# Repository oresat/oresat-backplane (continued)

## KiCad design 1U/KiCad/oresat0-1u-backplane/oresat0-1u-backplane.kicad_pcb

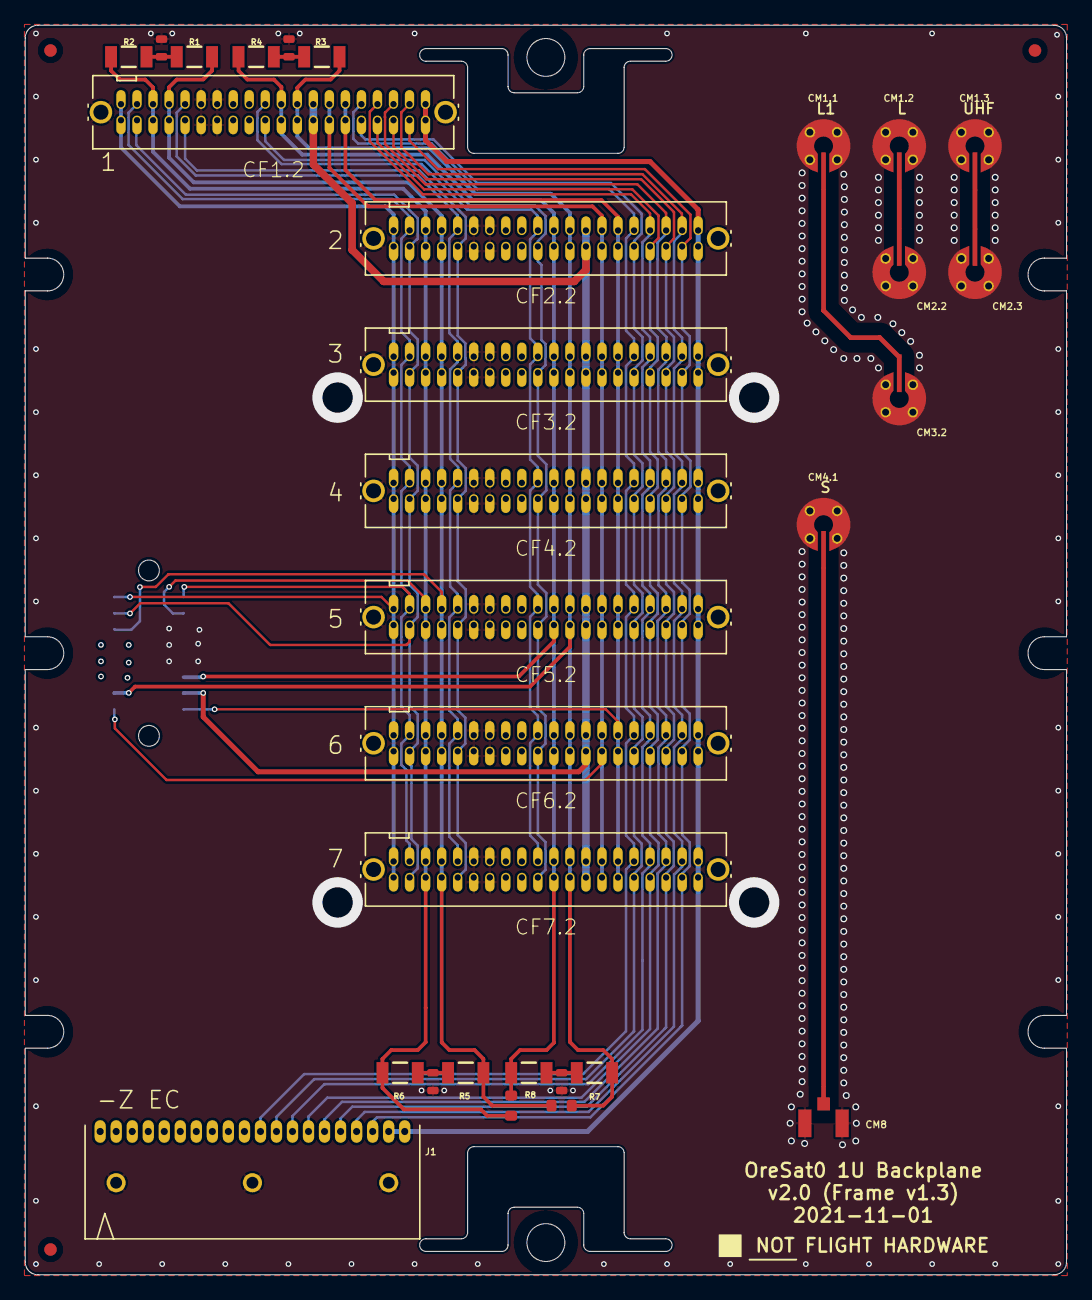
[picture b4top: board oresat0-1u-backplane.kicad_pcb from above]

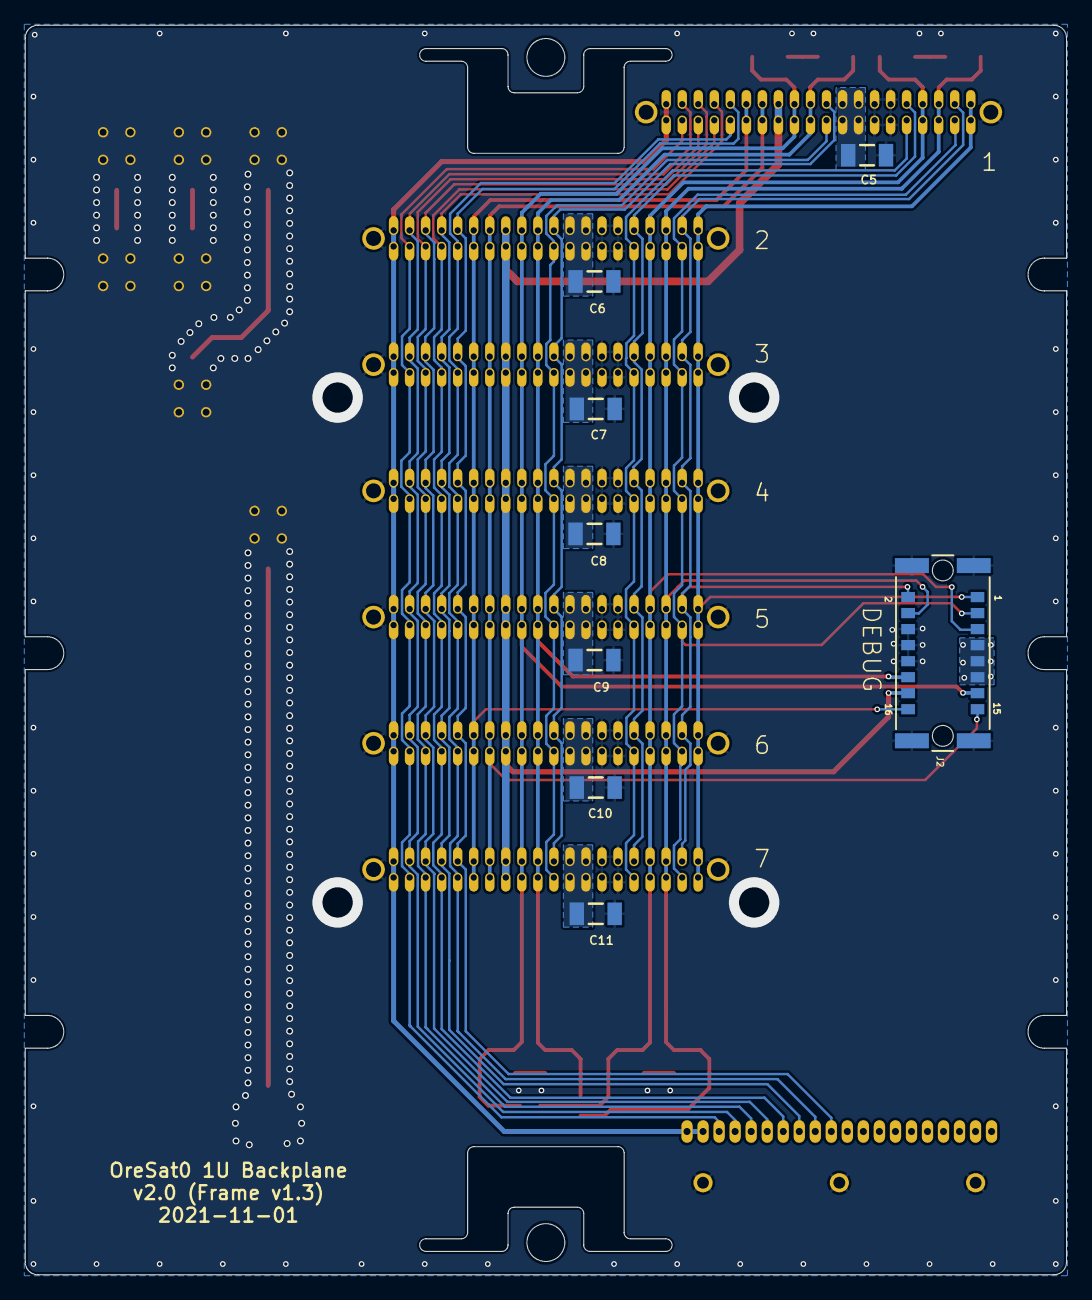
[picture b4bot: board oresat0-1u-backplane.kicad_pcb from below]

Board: 4 copper layers, 82.5 x 99.0 mm, 44 parts (8 on the bottom side), 33 nets.

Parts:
@HOLE0, @HOLE1: (no value)
C1, C2, C3, C4: 1n; .0603-C-NOSILK
C5, C6, C7, C8, C9, C10, C11: 10u 25V; 1206-B
CF1.2, CF2.2, CF3.2, CF4.2, CF5.2, CF6.2, CF7.2: SFM-120-X1-XXX-D
CM1.1, CM1.2, CM1.3, CM2.2, CM2.3, CM3.2, CM4.1: J-MOLEX-SMPM-73300-0111X; J-MOLEX-SMPM-73300-0111X-long
CM8: U.FL-R-SMA; U.FL-R-SMT
FIDUCIAL1, FIDUCIAL2, FIDUCIAL3: FIDUCIAL-1.0X2.0
J1: 5-104196-5
J2: M55-6001642R; CONN_M55-6001642R_HRW
R1, R2, R3, R4: 60.4; 1206-C
R5, R6, R7, R8: NP/60.4; 1206-C
R9, R10: 0; .0603-B-NOSILK
U$1: FLIGHMARKERNEW; FLIGHTMARKER_NEW_BOARDS

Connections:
C3-UART-RX: CF1.2.38, CF2.2.38, CF3.2.38, CF4.2.38, CF5.2.38, CF6.2.38, CF7.2.38, J2.2
C3-UART-TX: CF1.2.37, CF2.2.37, CF3.2.37, CF4.2.37, CF5.2.37, CF6.2.37, CF7.2.37, J2.3
CAN1_H: CF1.2.33, CF1.2.34, CF2.2.33, CF2.2.34, CF3.2.33, CF3.2.34, CF4.2.33, CF4.2.34, CF5.2.33, CF5.2.34, CF6.2.33, CF6.2.34, CF7.2.33, CF7.2.34, J2.5, R1.1, R5.1, R10.1
CAN1_L: CF1.2.35, CF1.2.36, CF2.2.35, CF2.2.36, CF3.2.35, CF3.2.36, CF4.2.35, CF4.2.36, CF5.2.35, CF5.2.36, CF6.2.35, CF6.2.36, CF7.2.35, CF7.2.36, J2.4, R2.1, R6.1, R9.1
CAN2_H: CF1.2.17, CF1.2.18, CF2.2.17, CF2.2.18, CF3.2.17, CF3.2.18, CF4.2.17, CF4.2.18, CF5.2.17, CF5.2.18, CF6.2.17, CF6.2.18, CF7.2.17, CF7.2.18, J2.13, R3.1, R7.1, R10.2
CAN2_L: CF1.2.19, CF1.2.20, CF2.2.19, CF2.2.20, CF3.2.19, CF3.2.20, CF4.2.19, CF4.2.20, CF5.2.19, CF5.2.20, CF6.2.19, CF6.2.20, CF7.2.19, CF7.2.20, J2.12, R4.1, R8.1, R9.2
GND: C1.2, C2.2, C3.2, C4.2, C5.2, C6.2, C7.2, C8.2, C9.2, C10.2, C11.2, CF1.2.27, CF1.2.28, CF1.2.29, CF1.2.30, CF1.2.LC1, CF1.2.LC2, CF2.2.27, CF2.2.28, CF2.2.29, CF2.2.30, CF2.2.LC1, CF2.2.LC2, CF3.2.27, CF3.2.28, CF3.2.29, CF3.2.30, CF3.2.LC1, CF3.2.LC2, CF4.2.27, CF4.2.28, CF4.2.29, CF4.2.30, CF4.2.LC1, CF4.2.LC2, CF5.2.27, CF5.2.28, CF5.2.29, CF5.2.30, CF5.2.LC1, CF5.2.LC2, CF6.2.27, CF6.2.28, CF6.2.29, CF6.2.30, CF6.2.LC1, CF6.2.LC2, CF7.2.27, CF7.2.28, CF7.2.29, CF7.2.30, CF7.2.LC1, CF7.2.LC2, CM1.1.GND (SHIELD1), CM1.2.GND (SHIELD1), CM1.3.GND (SHIELD1), CM2.2.GND (SHIELD1), CM2.3.GND (SHIELD1), CM3.2.GND (SHIELD1), CM4.1.GND (SHIELD1), CM8.2, CM8.3, J1.HD1 (HD), J1.HD2 (HD), J1.HD3 (HD), J2.6, J2.8, J2.10, J2.19 (17), J2.20 (17), J2.21 (17), J2.22 (17)
L1-TURNSTILE: CM1.1.RF-DOWN (RF), CM3.2.RF-DOWN (RF)
L-TURNSTILE: CM1.2.RF-DOWN (RF), CM2.2.RF-DOWN (RF)
unnamed: C1.1, R1.2, R2.2
unnamed: C2.1, R3.2, R4.2
unnamed: C3.1, R5.2, R6.2
unnamed: C4.1, R7.2, R8.2
OPD_PWR: CF1.2.15, CF1.2.16, CF2.2.15, CF2.2.16, CF3.2.15, CF3.2.16, CF4.2.15, CF4.2.16, CF5.2.15, CF5.2.16, CF6.2.15, CF6.2.16, CF7.2.15, CF7.2.16, J2.14
OPD_SCL: CF1.2.13, CF1.2.14, CF2.2.13, CF2.2.14, CF3.2.13, CF3.2.14, CF4.2.13, CF4.2.14, CF5.2.13, CF5.2.14, CF6.2.13, CF6.2.14, CF7.2.13, CF7.2.14, J2.15
OPD_SDA: CF1.2.11, CF1.2.12, CF2.2.11, CF2.2.12, CF3.2.11, CF3.2.12, CF4.2.11, CF4.2.12, CF5.2.11, CF5.2.12, CF6.2.11, CF6.2.12, CF7.2.11, CF7.2.12, J2.16
S-PATCH: CM4.1.RF-DOWN (RF), CM8.1
SPARE1-MAG-SDA: CF1.2.1, CF1.2.2, CF2.2.1, CF2.2.2, CF3.2.1, CF3.2.2, CF4.2.1, CF4.2.2, CF5.2.1, CF5.2.2, CF6.2.1, CF6.2.2, CF7.2.1, CF7.2.2, J1.19, J1.20
SPARE3-MAG-SCL: CF1.2.3, CF2.2.3, CF3.2.3, CF4.2.3, CF5.2.3, CF6.2.3, CF7.2.3, J1.18
SPARE4-MAG-SCL: CF1.2.4, CF2.2.4, CF3.2.4, CF4.2.4, CF5.2.4, CF6.2.4, CF7.2.4, J1.17
SPARE5-MAG-POWER: CF1.2.5, CF2.2.5, CF3.2.5, CF4.2.5, CF5.2.5, CF6.2.5, CF7.2.5, J1.16
SPARE6-MAG-POWER: CF1.2.6, CF2.2.6, CF3.2.6, CF4.2.6, CF5.2.6, CF6.2.6, CF7.2.6, J1.15
SPARE7: CF1.2.7, CF2.2.7, CF3.2.7, CF4.2.7, CF5.2.7, CF6.2.7, CF7.2.7, J1.14
SPARE8: CF1.2.8, CF2.2.8, CF3.2.8, CF4.2.8, CF5.2.8, CF6.2.8, CF7.2.8, J1.13
SPARE9-TURNSTILE-DEPLOY: CF1.2.9, CF2.2.9, CF3.2.9, CF4.2.9, CF5.2.9, CF6.2.9, CF7.2.9, J1.12
SPARE10-TURNSTILE-DEPLOY: CF1.2.10, CF2.2.10, CF3.2.10, CF4.2.10, CF5.2.10, CF6.2.10, CF7.2.10, J1.11
SPARE21: CF1.2.21, CF2.2.21, CF3.2.21, CF4.2.21, CF5.2.21, CF6.2.21, CF7.2.21
SPARE22: CF1.2.22, CF2.2.22, CF3.2.22, CF4.2.22, CF5.2.22, CF6.2.22, CF7.2.22
SPARE31: CF1.2.31, CF2.2.31, CF3.2.31, CF4.2.31, CF5.2.31, CF6.2.31, CF7.2.31
SPARE32: CF1.2.32, CF2.2.32, CF3.2.32, CF4.2.32, CF5.2.32, CF6.2.32, CF7.2.32
UHF-TURNSTILE: CM1.3.RF-DOWN (RF), CM2.3.RF-DOWN (RF)
VBUS: C5.1, C6.1, C7.1, C8.1, C9.1, C10.1, C11.1, CF1.2.23, CF1.2.24, CF1.2.25, CF1.2.26, CF2.2.23, CF2.2.24, CF2.2.25, CF2.2.26, CF3.2.23, CF3.2.24, CF3.2.25, CF3.2.26, CF4.2.23, CF4.2.24, CF4.2.25, CF4.2.26, CF5.2.23, CF5.2.24, CF5.2.25, CF5.2.26, CF6.2.23, CF6.2.24, CF6.2.25, CF6.2.26, CF7.2.23, CF7.2.24, CF7.2.25, CF7.2.26, J2.7, J2.9, J2.11
~SD: CF1.2.39, CF1.2.40, CF2.2.39, CF2.2.40, CF3.2.39, CF3.2.40, CF4.2.39, CF4.2.40, CF5.2.39, CF5.2.40, CF6.2.39, CF6.2.40, CF7.2.39, CF7.2.40, J2.1

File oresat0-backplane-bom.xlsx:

Bill Of Materials for OreSat0 1U Backplane
PCB version: 2.0 |  |  | P/NP = | Place/No Place
BOM revision: 1 |  |  | Generic = | Any part with the same characteristics may be substituted
Cnt | Part References | P/NP | Mfg | Mfg PN | Description | Distributor | Dist. PN | Cost | Ext. | Stock* | Generic | Notes
2 | C1, C2 | P | Murata | GCM1885C2A102JA16D | 1000 pF ±5% 100V Ceramic Capacitor C0G, NP0 0603 (1608 Metric) | Digi-Key | 399-C0603C102F1GACAUTOCT-ND | 0.14299999999999999 | 0.28599999999999998 | 0 | Y | High voltage, automotive grade
0 | C3, C4 | NP | Murata | GCM1885C2A102JA16D | 1000 pF ±5% 100V Ceramic Capacitor C0G, NP0 0603 (1608 Metric) | Digi-Key | 399-C0603C102F1GACAUTOCT-ND | 0 | 0 | 0 | Y
7 | C5, C6, C7, C8, C9, C10, C11 | P | Murata | GCM31CC71E106KA03K | 10 µF ±10% 25V Ceramic Capacitor X7S 1206 (3216 Metric) | Digi-Key | 490-14533-1-ND | 0.57499999999999996 | 4.0249999999999995 | 0 | Y | Vbus hold-up capacitors
7 | CM1.1, CM1.2, CM1.3, CM2.2, CM2.3, CM3.2, CM4.1 | P | Molex | 073300-0110 | "RF": SMPM Connector Plug, Male Pin 50 Ohm SMT + TH | Digi-Key | WM10770-ND | 14.02 | 98.140000000000001 | 8 | N | RF connectors
7 | B1, B2, B3, B4, B5, B6, B7 | P | Molex | 073300-0220 | Adapter Coaxial Connector SMPM Jack, Female Socket To SMPM Jack, Female Socket 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 | Digi-Key | WM17066-ND | 14.720000000000001 | 103.04000000000001 | 16 | N | RF barrel adapters (required)
7 | CF1.2, CF2.2, CF3.2, CF4.2, CF5.2, CF6.2, CF7.2, CF8.2 | P | Samtec | SFM-120-01-S-D-LC | "Main": TigerEye SFM series 40 pin 1.27 mm TH Vertical connector | Digi-Key | SAM11706-ND | 11.997999999999999 | 83.98599999999999 | 11 | N | Main card connectors
1 | J1 | P | TE | 5-104196-5 | 20 Position Receptacle Connector 0.050" (1.27mm) Through Hole, Right Angle Gold | Digi-Key | A115240-ND | 6.4299999999999997 | 6.4299999999999997 | 8 | N | -Z End Cap connector
1 | J2 | P | Harwin | M55-6001642R | 16 Position Receptacle Connector 0.050" (1.27mm) Surface Mount Gold | Digi-Key | 952-3836-1-ND | 1.96 | 1.96 | 6 | N | Debug connector
1 | PCB1 | P | Osh Park | N/A | OreSat0 1U Backplane v2.0 | N/A | N/A | 126.59999999999999 | 126.59999999999999 | 3 | N | 4 layer Osh Park PCB
4 | R1, R2, R3, R4 | P | Rohm | ESR18EZPF60R4 | 60.4 Ohms ±1% 0.5W, 1/2W Resistor 1206 AEC-Q200 | Digi-Key | RHM60.4AFCT-ND | 0.126 | 0.504 | 0 | Y | High wattage just in case
0 | R5, R6, R7, R8 | NP | Rohm | ESR18EZPF60R4 | 60.4 Ohms ±1% 0.5W, 1/2W Resistor 1206 AEC-Q200 | Digi-Key | RHM60.4AFCT-ND | 0.126 | 0 | 0 | Y | High wattage just in case
2 | R9, R10 | P | Stackpole | RMCF0603ZT0R00 | 0 Ohms Jumper 0.1W, 1/10W Chip Resistor 0603 (1608 Metric) Automotive AEC-Q200 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 | Digi-Key | RMCF0603ZT0R00CT-ND | 0.10000000000000001 | 0.20000000000000001 | 0 | Y | CAN jumpers (bridges CAN1 to CAN2)
 |  |  |  |  |  |  |  | Total: | 425.17099999999999
BOM Version Information
Rev | Date | Notes
1.0r0 | -- | Initial BOM for 1U.
1.1r0 | 44173 | Added -Z end cap connector, and debug connector.
2.0r0 | 44486 | v2.0 backplane specifically for OreSat0
2.0r1 | 44525 | Fixed debug connector.
* Stock: | 44501 | Last updated before OreSat0.1 orders

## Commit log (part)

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2016-03-11 README file
2016-03-11 initial commit with board outline, holes, and first three connectors
2016-03-26 Updated backplane to latest connectors - 1.27 mm 2x20 and new MCX connectors. Also added keep outs from Jeremy.
2016-03-26 Updated to TE MCX M verticals to save precious, precious mm on the cards
2018-08-19 Latest backplane, with SamTec TigerEye SFM-1x0 connectors, and with MMCX to UT-047 RF connectors.
2018-08-19 Beginnings of the 20 slots, with connectors! Almost Joe Approved, waiting for better DXF.
2018-08-20 OMG we have a backplane. Note that the MMCX connectors are probably incorrectly placed because we're going to switch to some different connector that's more SMT-y for Oliver because he's an RF racist.
2018-09-11 Backplane v1.0. Finally. Uses SMPM RF connectors.
2018-09-11 Added connector specs to the README file.
2018-09-11 Added .gitignore file.
2018-09-17 Updated center fasteners with new precision shoulder bolt diameter and spring-like arm.
2018-10-02 Version 1.0 of backplane. With SMPM connectors, with the correct BSTOP layer for thermal connection to the -X frame, and with separate pins on the backplane connectors for future flexibility in this 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
2018-10-02 Ground stitching. Probably don't need it, but...
2018-10-02 Updated README with image and added explicit license.
2018-10-02 Fixed formatting.
2018-10-02 Minor cleanup.
2018-10-02 Added aux conncetor info.
2018-10-02 OOps, need a BOM.
2018-12-03 Updated TFM connectors with smaller holes and bigger pads based on the v1.0 backplane. Now it's V1.1!
2019-01-15 Backplane v1.1. Main connectors to all cards including end cards, Aux connector to all cards but the end card, signals named, etc.
2019-01-15 Oh right, stitching on the ends.
2019-01-15 Updated picture and readme.
2019-02-22 Fixed wrong signal names, removed thermals from bottom of main connectors, should be ready for fab.
2019-05-26 Backplane v3. All good, except for the polygon error that keeps killing EAGLE. I thought this was fixed? Also, the RF stuff is all terrible until Vigely fixgures out what we should do :)
2019-06-20 Updated connector locations from MCAD. Last of the separate RF grounds before reverting back to single ground plane.
2019-06-29 Backplane v2.0! New dimensions and connector placement for Frame v1.1. New bespoke RF lines for the current OreSat RF card and antenna plan. After design review, added one more pin pair to vbus and g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
2019-06-29 Updated microstrips to 0.38 mm based on theoretical calcs of 0.35 mm for the OSH Park 4 layer, and Harmon Industry's measurements of 0.41 mm for 50 ohms. Also expanded solder mask openings around RF 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
2019-07-01 Last polish before fab. Removed copper and solder mask from the fasteners that don't make electrical contact, so they can be cycled without flaking and other damage.
2019-07-24 Updated to latest backplane DXF. Reduced all sides by 0.15 mm. Fixed solar connector cutout areas that were lopsided. Awaiting RF testing.
2019-08-20 "auto-generated from update_repos.py"
2019-11-01 added oresat grounding block diagram
2020-02-16 More additions to v2.1: split termination on the CAN busses, locked everything down, and moved the RF connectors to where they're currently supposed to be.
2020-02-16 Updated BOM for v2.1.
2020-07-13 Created OreSat0 1U backplane from 2U backplane.
2020-07-13 Widended shoulder bolt screw down area to cover the entire bolt. Shouldn't affect anything.
2020-07-13 oresat-backplane-1u.sch
2020-07-13 Uh, whoops, should have committed these at the same time. First draft of the 1U backplane. Passes ERC and DRC.
2020-07-20 TNAMES cleanup, renamed by card number.
2020-08-01 Cleaned up README and BOMs for 1U and 2U backplanes.
2020-08-26 Added 1U -Z end cap connector.
2020-08-26 Added -Z end cap connector to 1U
2020-08-28 Backplane v1.1!
2020-11-17 Updated 1U backplane to v1.2. Better position of end cap connector, added debug connector.
2020-12-08 Final tweaks to v1.2 - off to fab.
2020-12-08 Updated with corrected debug connector. Footprint didn't change, so no change to version.
2020-12-09 First cut of the debug port hat.
2020-12-11 Added debug connector to 1U BOM.
2020-12-11 First rev of debug port breakout.
2021-03-22 Version 1.3. No significant difference with v1.2 besides added TPLACE block, updated not for flight marker, and fiducials just in case.
2021-03-22 v1.1 debug port breakout. v1.0 wasn't deep enough so it hit the solar panel.
2021-03-22 v1.1 of the debug port plug. Perhaps it's not a great to short out literally every pin on the bus to ground? Maybe?
2021-10-03 Backplane v2.0. Changes to signals; vaguely back compatible with v1. Also spun off OreSat0 bespoke backplane for the OreSat0 mission.
2021-10-18 Final OreSat0 1U backplane and new BOM.
2021-11-03 OreSat0 1U backplane; as manufacutred 2021-11-01
2021-11-11 Minor BOM formatting.
2021-11-11 Updated spare lines in schematic to reflect magnetometer usage; no change to board.
2022-02-06 Repo cleanup since we're moving to KiCAD, and sorting by U.
2022-02-06 Half-done changes to the 2U (needs fixing, but in KiCAD).
2022-02-06 Add HASP mission backplane (never used).
2022-02-06 Added note on HASP, added CERN OHL 2.
2022-02-06 REmoved 1U v1.1 debug port; moved to flatsat repo.
2022-02-06 Added debug connector information.
2022-02-06 Updated PNG of 1U to OreSat0!
2022-06-29 Moved 2u-hasp backplane to KiCad
2022-06-29 Fixed microstrip clearance
2022-07-06 Migrated 1u to KiCad
2022-07-07 Moved the correct 2u backplane to KiCad this time
2022-07-13 RF traces are fixed, hopefully correctly
2022-07-15 Made the DRC happy with better RF footprints
2022-07-15 Fixed symbol library
2022-07-18 Fixed DRC errors and warnings
2022-07-27 Rearranged the RF connectors for Oresat0.5
2022-07-27 Updated 2u backplane connector stuff
2022-07-27 Fixed RF traces and connectors, and DRC
2022-07-27 Updated silkscreen to use layout title
2022-07-27 Changed title block
2022-07-29 Aligned everything to the DXF, should maybe be done I think
2023-02-19 Big reorg for OreSat0.5, update .gitignore.
2023-02-19 Created Oresat0.5 backplane
2023-02-19 Added end mounting holes and CAN connector resistors
2023-02-19 Fixed all (most) of the issues from Eagle imports
2023-02-19 Moved entire schematic to single page
2023-02-19 Cleaned up OreSat0.5 backplane folder
2023-02-20 Fixed backplane connector library names
2023-02-20 Fixed silkscreen on copper
2023-02-20 Updated 2U DXF to something more useful, and rename Ben's naming faux pas.
2023-02-20 Removing unecessary files.
2023-02-20 Update CAM settings for building Gerbers.
2023-03-28 Added S/N block and updated to KiCad7
2023-03-28 Moved aux connectors, fixed RF connector soldermask
2023-04-23 Removed soldermask around mounting screws
2023-04-25 Polished v1.1 of the OreSat0.5 backplane: fixed schematic off grid issues and updated symbols, removed copper spikes, updated date, ignored ignorable DRC errors.
2025-09-29 New OreSat1 2U backplane. Switched to the correct backplane design (OreSat0.5 was incorrect) and broke up into multiple sheets. Set actual part numbers for BOM, added symbols for fastener holes. Stil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
2025-10-04 Started 3U design
2025-10-05 Most current version
2025-10-05 Fixed
2025-10-08 Rough draft
    Lots more cleaning up to be done
2025-10-09 Update of OreSat1 2U backplane. Removed extraneous connectors, imported DXF from OnShape and moved debug connectors by 0.176 mm. Routing left to do.
2025-10-14 Updated DXF to latest (still no solder mask) and finished routing based on new card placements.
2025-10-21 Most up to date
2025-10-22 Added latest DXF drawing from the structure team, updated the stackup with OreSat standards, updated the page sizes, etc.
2025-10-22 Actually commit all of the files created for the scheamtic :/
2025-10-22 Remove zip file
2025-10-22 Fixed libraries and footprints, synced sch and pcb (sorry Jacob).
2025-10-22 Fix library issues on aux footprints.
2025-10-22 Added example aux connectors.
2025-11-21 Connectors placed & zoned
2025-11-21 Added more Auxiliary connectors
2025-11-23 Connectors laid out, unrouted
2025-11-23 Update .gitignore file with autosave temp file.
2025-11-30 Added traces between main connectors, RF cons labelled, vbus zones set
2025-12-02 Fixed DRC errors
2025-12-02 Moved can lines to back & fixed RF schematic organization
2025-12-04 Can lines on back - need to move can resistors to front & add b.side solder mask
2025-12-04 Back solder mask added & can resistors moved to F.cu. Final
2025-12-04 Disconnected RF DRC violations excluded
2025-12-29 OreSat1 backplane v1.0 commit
    Final cleanup. moved should bolt holes from to drilled holes, not routed holes. Updated date on schematic and board. Sending out for fab.
2026-02-07 Removed deployables and turned them into spares.
2026-02-21 new dir w ESI changes v1
    may need to redo RF
2026-02-21 Added schematic and board variables, polished some silkscreen, reviewed board, renamed directory
2026-02-21 Added fastener solder mask cutouts and copper keep out zones for all fasteners.
2026-02-21 Updated generic 3U backplane with correct fastener copper and solder mask cutouts under fastners, and updated date on sch and brd.
2026-02-21 Removed refdes for holes. Silly.
2026-02-22 Labelled connectors & disconnected C3 LBand
2026-02-22 fixed erc and drc errors
2026-02-22 changed file org
2026-02-22 Polish of 3U for ESI
    Fixed ERC/DRC/sync errors. Made fancy RF table. Fixed BOM.
2026-02-22 Update date!
2026-02-22 Cleaned up the files Shae was trying to clean up
2026-02-22 Add some automation to the 3U build
2026-02-22 Better documentation on Makefile
2026-02-22 OreSat1 backplane v1.1
    Lots of little changes; technically there should be no actual changes betwen v1.0 and v1.1 but
    the BOM is correct, the masks are done better, the precision shoulder bolts are drills not
    routed, and it's just cleaned up a lot.
2026-02-22 Upgrade makefile; now fully automatic, finds the local project name
2026-02-22 Upgrade makefile to latest and changed bom presets to match
2026-02-24 Adding DXF of 3U backplane
2026-02-26 ESI backplane edge cut changes & naming changes
2026-02-27 updated microstrips around cutout
2026-02-27 Final polishing of ESI backplane and updated Makefile
2026-03-05 Changed schematic & pcb to add spare traces, no helical or turnstile
2026-03-05 Update makefile
2026-03-05 Changed DNP for SDR control board
2026-03-06 Renamed ESI backplane
2026-03-09 Version 1.1 of the ESI OreSat backplane
    Lots of cleanup for the automated build, including adding READMEs and fiducials! Ready for fab!
2026-03-09 Small fix for CAD directory
2026-03-09 Zip the CAD file too
2026-03-09 build file and updated footprints
2026-03-09 footprint weirdness fixed
2026-03-09 fixed resistor footprint issues?
2026-03-12 Fixed minor BOM issue with a repeated connector.
2026-03-12 Minor BOM fix on 2U
2026-03-12 Updated makefile
2026-04-01 Switch C3 and SBand card, GPS now under C3 -- Needs review
2026-04-03 Added solder paste to RF Connectors
2026-04-05 updated spare lines on schematic & began tracing
    a little more than halfway through
2026-04-05 More routing
2026-04-06 Board switches and microstrip mask change
2026-04-08 Moved RW and mag cards back, changes spare tracing side -- updated DNP w changes
2026-04-08 Fix and update SMPM connectors, now they're sane for KiCad. Also, move to DRU-based ground plane peelback to avoid DRC errors, and improve fmask layer. Also lock a bunch of stuff that ought to be loc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
2026-04-08 minor f mask fix around SMPMs
2026-04-09 more stitching, updated date, updated makefile and README
2026-04-09 Star tracker connect added, got rid of SDR
2026-04-26 Connected Spares and switched OPD to inner layer. Updated RF cons -- **RF con new footprint has ground pad schematic parity error
2026-04-26 Updated schematic symbol for RF con. Believe this is done. Remaining DRC errors are only unconnected RF cons -- fine until use defined for non-generic version.
2026-04-26 remove .history files
